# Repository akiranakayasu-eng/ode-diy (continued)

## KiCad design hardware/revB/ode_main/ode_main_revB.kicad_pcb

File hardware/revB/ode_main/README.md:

# ode_main rev B（ESP32-S3 Wi-Fi 一体版）回路図 6 版・PCB 4 版（2026-11-23）

構成案: 構成案_revB_ESP32-S3_v1.md（同じフォルダ）。ケースは case/ と 構成案_revB.md（v0）。

## 状態

- 回路図 6 版: ERC 0（kicad-cli 10.0、docker）、設計意図との照合 0（verify.txt: 365 ピン / 70 ネット）。6 版は 5 版に R87 を足しただけ
- 1 版は別スレッドでチェック済み（回路図チェック_別スレッド_2026-11-19.md、高 0・中 4・低 9）。2 版の変えた所も別スレッドでチェック済み（変更点チェック_2版_別スレッド_2026-11-19.md、高 0・中 1・低 4）。3 版の変えた所も別スレッドでチェック済み（変更点チェック_3版_別スレッド_2026-11-19.md、高 0・中 0・低 3）。4 版はその低 3 件を直した版で、4 版の変えた所も別スレッドでチェック済み（変更点チェック_4版_別スレッド_2026-11-19.md、高 0・中 0・低 1。低 1 は下の残りの確認 4）。5 版は天板へ出る線に保護を足した版で、**5 版で変えた所は別スレッドのチェック待ち**（PCB のチェックと一緒に頼む）
- PDF: ode_main_revB.pdf
- PCB 1 版は別スレッドでチェック済み（PCBチェック_1版_別スレッド_2026-11-23.md、高 0・中 5・低 11。5 版の回路図の変えた所は中以上なし）
- PCB 2 版は別スレッドで変えた所をチェック済み（変更点チェック_PCB2版_別スレッド_2026-11-23.md、高 0・中 0・低 7）
- PCB 3 版（2026-11-23）: 2 版のチェックの低 2・3・6 を直した版。変えた所は別スレッドでチェック済み（高 0・中 0・低 1）
- PCB 4 版（2026-11-23）: 3 版のチェックの低 1 を直した版。下の「PCB 4 版で変えた所」。変えた所と SPI・UART の配線は別スレッドでチェック済み（高 0・中 0・低 3、下の「PCB 4 版のチェックで残した点」）。部品の購入・基板の発注は延期中

## 中身

| 部分 | 部品 | 内容 |
|---|---|---|
| マイコン | U1 ESP32-S3-WROOM-1-N16R8 | 3V3 に 22µF + 0.1µF、EN に 10k/1µF（データシート図 7）。SW1 RESET（EN）、SW3 BOOT（IO0） |
| 有線 LAN | U3 W5500、Y2 25MHz、J5 RJMG1BD3B8K1ANR | WIZnet W5500-Ref-RJ45WithMag に合わせた。SPI は IO10 CS / IO11 MOSI / IO12 SCLK / IO13 MISO、IO14 INT、IO9 RST |
| DMX | U7・U9 74AHCT1G125、U11 ADM2587E、J11 XLR3、J12 XH3 | IO17 = TX（R82 0Ω を通して TX_M、R78 プルアップ）、IO21 = DE（R74 プルダウン）。rev A と同じ周辺 |
| 電源 | J1 USB-C、U5 USBLC6、F1 PICOSMDC110S-2（秋月 113955、1.1A・6V、0805。rev B 構成案 v0 の決定）、Q1 突入制限、U6 MCP1826 | rev A と同じ。FB2 で W5500 の AVDD（+3V3A）を分ける |
| 天板 | J6 JST PH 8P | 1 +3V3 / 2 GND / 3 EN_PANEL / 4 BTN_LOCK / 5 LED_LAN / 6 LED_DMX / 7 LED_LOCK / 8 予備。LOCK は R83 1k＋C78 100n、LED は R84〜R86 100Ω を通して IO4〜IO7 へ。天板の回路図は ../ode_top_revB |
| その他 | D4 PWR、D6 STAT（IO18）、J4 UART0 ログ（R77 499Ω）、CC1/CC2 を R80・R81 22k を通して IO1/IO2 の ADC へ（C74・C75 100n） | |

ピン割り当ての理由と出典は構成案の「ピン割り当て案」。IO35〜37（PSRAM）と IO0・IO3・IO45・IO46（起動ピン）の扱いもそこに書いた。

## 2 版で変えた所（1 版のチェックを受けて）

| 指摘 | 変えた所 |
|---|---|
| 中 1 | U3 23 番（RSVD）を GND へ（W5500 データシート表 2「must be tied to GND」） |
| 中 2 | 受信の終端 R71・R72 を W5500 側（ETH_RXP・ETH_RXN）と RCT の間へ移した（WIZnet 参考回路のとおり） |
| 中 3 | F1 の値を PICOSMDC110S-2 にした（0805 は rev B 構成案 v0 の決定どおり。秋月 113955: 1.1A、トリップ 2.2A、6V） |
| 中 4 | 天板の J6.3 は R79 1kΩ を通して EN へ（ネット EN_PANEL） |
| 低 1 | DE を IO18 → IO21、STAT を IO21 → IO18 に入れ替え |
| 低 2 | TX_M に R78 10k プルアップ |
| 低 3 | USB D+／D− に R4・R5（0Ω）、ネット USB_DP_M・USB_DM_M |
| 低 4 | W5500 SCLK に R76（0Ω）と C69（未実装） |
| 低 5 | UART0 TX に R77 499Ω |
| 低 6 | W5500 XO と水晶の間に R62（0Ω） |
| 低 8 | CC1・CC2 を IO1・IO2（ADC）へ |
| 低 7・低 9 | 低 7（R8 は rev A と同じ GND）は変えない。低 9（LDO の発熱）は PCB で見る |

## 3 版で変えた所（2 版の変更点チェックを受けて）

| 指摘 | 変えた所 |
|---|---|
| 中 1 | CC1・CC2 と IO1・IO2 の間に R80・R81（22k）、ESP32 側に C74・C75（→ GND。3 版は 10nF、4 版で 100nF）。ネット CC1_ADC・CC2_ADC |
| 低 1 | R60 1MΩ を X25_IN–X25_XO（W5500 の XI–XO ピンの間）へ移した（W5500 図 3、WIZnet 参考回路） |
| 低 2 | USB D+／D− に C76・C77（未実装、→ GND）の場所（3 版は ESP32 側、4 版でコネクタ側へ） |
| 低 3 | IO17（ネット TX_U）と TX_M の間に R82（0Ω） |
| 低 4 | J4 の GND を右へ出して、ラベルと重ならないようにした（見た目だけ） |

## 4 版で変えた所（3 版の変更点チェックを受けて）

| 指摘 | 変えた所 |
|---|---|
| 低 1 | C76・C77 を USB_DP・USB_DM（R4・R5 と U5 の間、コネクタ側）へ移した（設計ガイドの USB の図、モジュールの図 7） |
| 低 2 | C74・C75 を 10nF → 100nF（設計ガイド ADC「0.1 μF」） |
| 低 3 | J6 の GND を右へ出して、ラベルと重ならないようにした（見た目だけ） |

## 5 版で変えた所（2026-11-23、作ったスレッドで足した）

| 理由 | 変えた所 |
|---|---|
| 天板は手で触れる板なので、ケーブルの先のピンを ESP32 に直結しない（2 版チェック中 1 と同じ考え） | J6.4 BTN_LOCK と IO7 の間に R83 1k、IO7 側に C78 100n（ESD とチャタリング）。ネット BTN_LOCK_M |
| 同上 | J6.5〜7 の LED 線と IO4〜IO6 の間に R84〜R86 100Ω。ネット LED_*_M。LED の電流は 680＋100Ω で約 1.7mA |

## PCB 4 版のチェックで残した点（低 3、どれも直さずに残した）

1. 裏の MISO が W5500 の水晶の真下を通る。間に内層の GND と +3V3 があるので影響は小さい。
2. SCLK の直列抵抗 R76 が W5500 側にある。ダンピングの抵抗なら ESP32 側が良い。今は 0Ω なので実害はない。必要になったら次の版で寄せる。
3. UART の 2 本がモジュールの下をアンテナと平行に約 16mm 通る。ログ用で低速なので、そのままにした。

## PCB 4 版で変えた所（PCB 3 版チェック 低 1）

| チェックの項目 | 変えた所 |
|---|---|
| 裏の GND ベタの細長い切れ端の上側約 24mm にビアがない | その上側は幅 0.3mm でビアが打てなかった。外層の GND ベタの最小幅を 0.25 → 0.5mm にして、細い帯を塗らないようにした。残った 16mm の部分にはビアが 3 本。切れ端用のビアは長さ 6mm に 1 本以上にした |
| 上の変更で C74・C75 の GND（裏、モジュールの下）に裏のベタが届かなくなった | C74.2 と C75.2 を裏の 0.4mm の線でつなぎ、間に GND ビア (5.04, 81.2) を足した |

- 結果: 未配線 0、DRC エラー 0（警告 5 は同じ種類）、verify_pcb NG 0。配線は作り直したので SPI・UART などの線の道筋は 3 版と少し違う

## PCB 3 版で変えた所（PCB 2 版チェックを受けて）

| チェックの項目 | 変えた所 |
|---|---|
| 低 2 1V2O の線が 21.5mm | 22 番から本体の内側のビア (26.1, 35.9) で裏へ落とし、裏の C53.1 へ手で引いた。5.7mm・ビア 1（gen_pcb.py の V12_ROUTES） |
| 低 3 裏の GND ベタの細長い切れ端 | 塗ったあとに GND のつなぎビアを打つ処理を足した（gen_pcb.py の gnd_stitch）。表裏とも GND のところに 5mm おきに 56 本、ビアが 1 本以下か、長いのに 2 本以下の切れ端に 2 本。裏の切れ端は無くなった |
| 低 6 README の数字 | モジュールの左端を 1.5mm に直した |

- そのままにした所: 低 1 J1 の A4/B9 側の VBUS（0.2mm とビア 4。主な電流は A9/B4 側の太い線を流れ、枝は 0.3A 以下）、低 4 USB の D+／D− のビアの数の差（フルスピード）、低 7 ケースと天板（ケースの奥行きの決定を待って直す）、R77 を U1.37 の近くへ（ログ用で低速）
- 組み立ての順番（低 5）: U1 の下の裏に R32・R80・R81・C74・C75 がある（C78 と C31 もモジュールのすぐ横の裏）。**裏の小物を先に付け、ESP32 モジュールは最後に上からホットガンで付ける**。ホットプレートで下から温めない
- 結果: 未配線 0、DRC エラー 0（警告 5 は同じ種類）、verify_pcb NG 0

## 回路図 6 版で変えた所（PCB 1 版チェック 低 11）

| 理由 | 変えた所 |
|---|---|
| BTN_LOCK が ESP32 の内部プルアップだけだった | R87 10k（+3V3 → BTN_LOCK_M）を足した |

## PCB 2 版で変えた所（PCB 1 版のチェックを受けて）

| チェックの項目 | 変えた所 |
|---|---|
| 中 1 アンテナが基板の角にない | U1 を左後ろの角へ (10.5, 77.25, 180°)。モジュールの外形の左端は基板の左端から 1.5mm（パッドの外端は 1.0mm）、アンテナ部は後ろの辺の外。後ろ左の取り付け穴をやめ、穴は (3.5, 59.5)・(72.5, 58)・(72.5, 80.5)・(49.5, 80.5) |
| 中 2 5V の経路が 0.2mm とビア 1 個 | J1 VBUS → F1 → C1 → Q1 → C3 を F.Cu の手引きで 0.5〜0.8mm（ビアなし）。C3 から U6 の入力までは F.Cu の +5V ゾーン |
| 中 3 LDO の出力がビア 1 個で +3V3 の面へ | U6 の 3 番と C5 を F.Cu の +3V3 ゾーンでつなぎ、In2 へのビアを 5 個 |
| 中 4 LDO の放熱の銅がない | U6 のタブ（GND）の周り約 10 × 10mm を F.Cu の GND ゾーン（直結）にし、In1 へのビアを 21 個 |
| 中 5 TOCAP C54 が遠い | C54 と C53（1V2O）を U3 の 20・22 番の裏へ。距離 1.1mm・2.6mm（1 版は 6.9mm） |
| 低 1 水晶が遠い | Y2 を 30・31 番の真下へ、R60・R62 も寄せた。X25 の配線は 3.5〜8mm でビアなし（1 版は 13〜17mm・ビア 2） |
| 低 4 外層に GND ベタがない | F.Cu と B.Cu の一次側に GND ベタ（優先度は一番下） |
| 低 5 J4・J6 がアンテナの近く | J4 は (22, 60)、J6 は (31.5, 71)。アンテナ部から 10mm 以上 |
| 低 7 シルク | 「ISOLATION 2.5kV」→「ISO」、アンテナの矢印 →「ANTENNA: back edge」、Art-Net の文字をやめて「DMX512 node」 |
| 低 11 | R87 を R83〜R86 の列に置いた（C78 は R83 と R84 の間の裏） |

- 合わせて動かした所: BOOT の SW3 は (35.5, 57)、R32 は 27 番の横の裏、CC の分圧 R80・R81・C74・C75 はモジュールの下の裏、SPI の R76・C69・R66 は U3 の下 (y 49) へ（32〜36 番の引き出しを空けるため）
- 結果: 未配線 0、DRC エラー 0（警告 5 は 1 版と同じ種類）、verify_pcb NG 0
- そのまま残した所: 低 2 Ethernet の対の長さの差（同じ）、低 3 USB 約 80mm（J1 が左前のため。1 版は 108mm）、低 6 C109 の沿面、低 8 AVDD のパスコン 4mm 前後、低 9 LED の色と抵抗（天板の LED を決めてから）、低 10 J6.1 に +3V3 をそのまま出す（天板側で受ける）

## PCB 1 版（2026-11-23、作ったスレッドでの確認まで）

- 76 × 84mm、4 層 FR-4 1.6mm（F.Cu・B.Cu 信号、In1 GND、In2 +3V3）。前の辺に左から USB-C J1、RJ45 J5、XLR3 J11（rev A の左 76mm と同じ位置）。ポート 1 の絶縁の島と帯も rev A と同じ寸法
- U1 ESP32-S3-WROOM-1 は後ろの辺に 180 度で置き、アンテナ部 6mm を基板の外へ出した（ESP32-S3 ハードウェア設計ガイド）
- W5500 U3 は RJ45 の後ろ。1〜12 番（TX/RX）を RJ45 側、水晶と SPI を U1 側に向けた
- U6（LDO）は左の後ろ、F1 は左の前（36mm 離した。docs/電流の見積もり_revB.md）
- 取り付け穴 M3 は (3.5, 45)・(72.5, 58)・(3.5, 80.5)・(72.5, 80.5)（基板の左上が原点、mm）。前の 2 つはコネクタと絶縁の島を避けて後ろへずらした。天板と底板もこれに合わせる
- 自動配線（scripts/route.py、rev A と同じ A*）で未配線 0。DRC はエラー 0、警告 5（U1 と J11 のシルクが基板の端で切れる 4、U1 の EP のビア穴を 0.2→0.3mm にしたためのライブラリとの差 1）
- verify_pcb.txt: パッドのネット照合、ベタのパッドのビア、パスコンの距離、SMD パッドの中のビア 0
- 気になる点（チェックで見てほしい）: Ethernet の対の長さの差（RXP 19.0mm／RXN 12.2mm、RDP 16.5mm／RDN 10.0mm）、USB D+／D− が約 108mm（J1 が左前、U1 の USB ピンが右側のため）、U6 の放熱の銅（まだ広げていない）
- 作り直し: docker kicad/kicad:10.0 の中で `sh scripts/all.sh`（geom → 配線 → 基板 → DRC → 照合）。絵は `bash scripts/render.sh`

## 残っている確認

1. 3.3V の合計電流と U6 の発熱（見積もりは docs/電流の見積もり_revB.md）（ESP32-S3 ピーク 355mA ＋ W5500 約 128mA ＋ LED。5V→3.3V で 1W 近くになりうる）。PCB で放熱の銅を取るか、降圧に替えるか。
2. RJMG1BD3B8K1ANR のトランス仕様（巻数比・インダクタンス）を Amphenol の図面で確かめる（作業環境から読めない）。
3. 天板の基板の回路図は ../ode_top_revB（2026-11-23）。天板の PCB はまだ。
4. F1 の保持電流は 25℃ 1.1A、60℃ 0.8A（秋月 113955 の表、4 版チェックで確認）。5V の合計電流（U6 の 3.3V 側、U11 ADM2587E、U7・U9）を出し、PCB で F1 を LDO から離して置くか、保持電流が上の品にするかを決める。

## 作り直し方

```
export KICAD_SYMDIR=<KiCad 10 の symbols フォルダ>
python3 scripts/gen_sch.py     # 1 回目で .kicad_sym、2 回目で回路図
sh run_erc.sh                  # ERC・ネットリスト・PDF・照合（docker kicad/kicad:10.0）
```

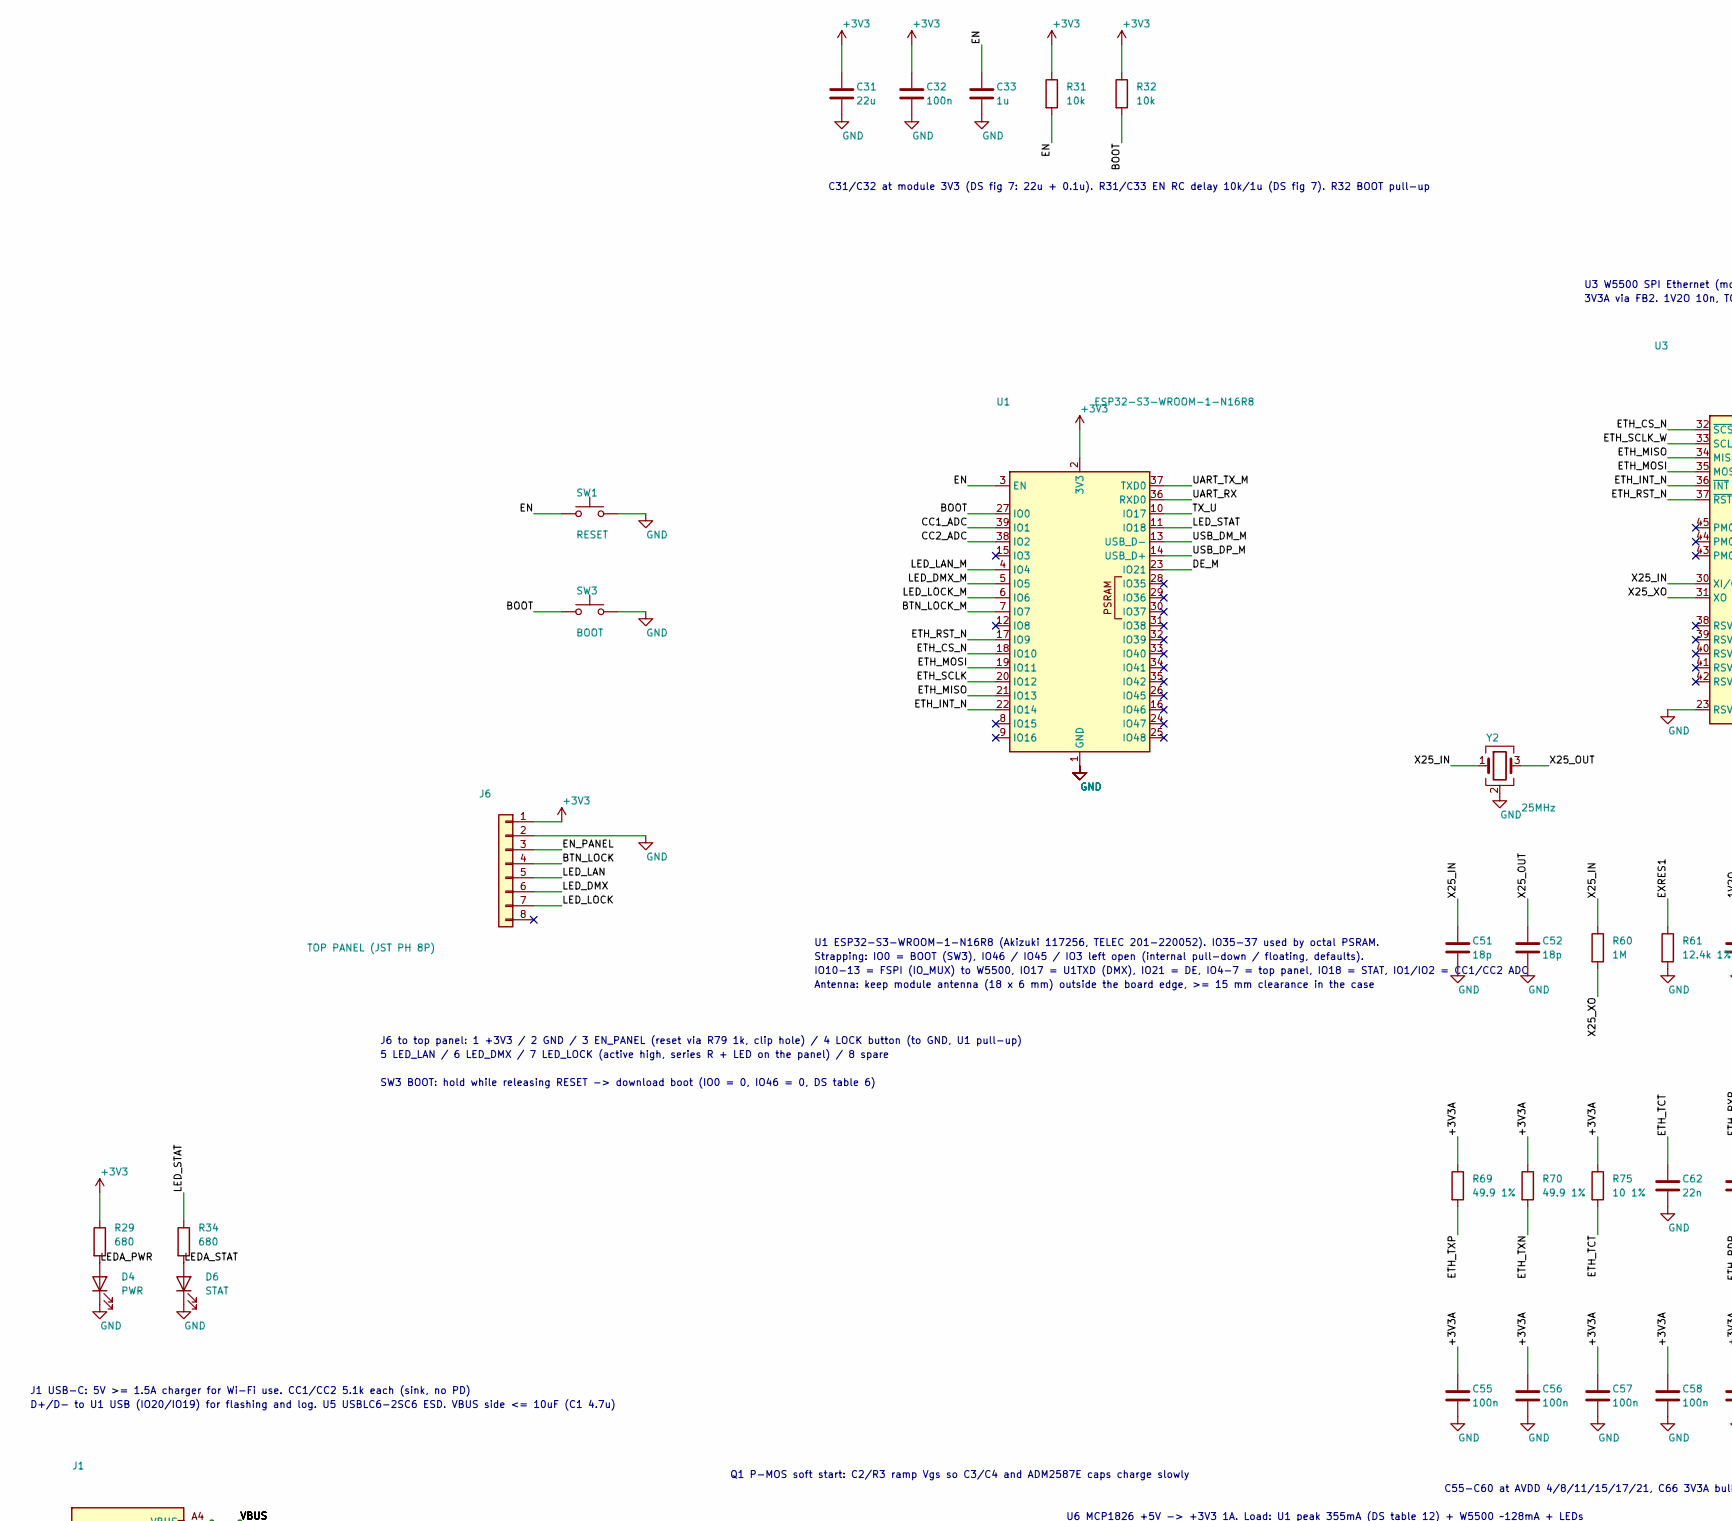
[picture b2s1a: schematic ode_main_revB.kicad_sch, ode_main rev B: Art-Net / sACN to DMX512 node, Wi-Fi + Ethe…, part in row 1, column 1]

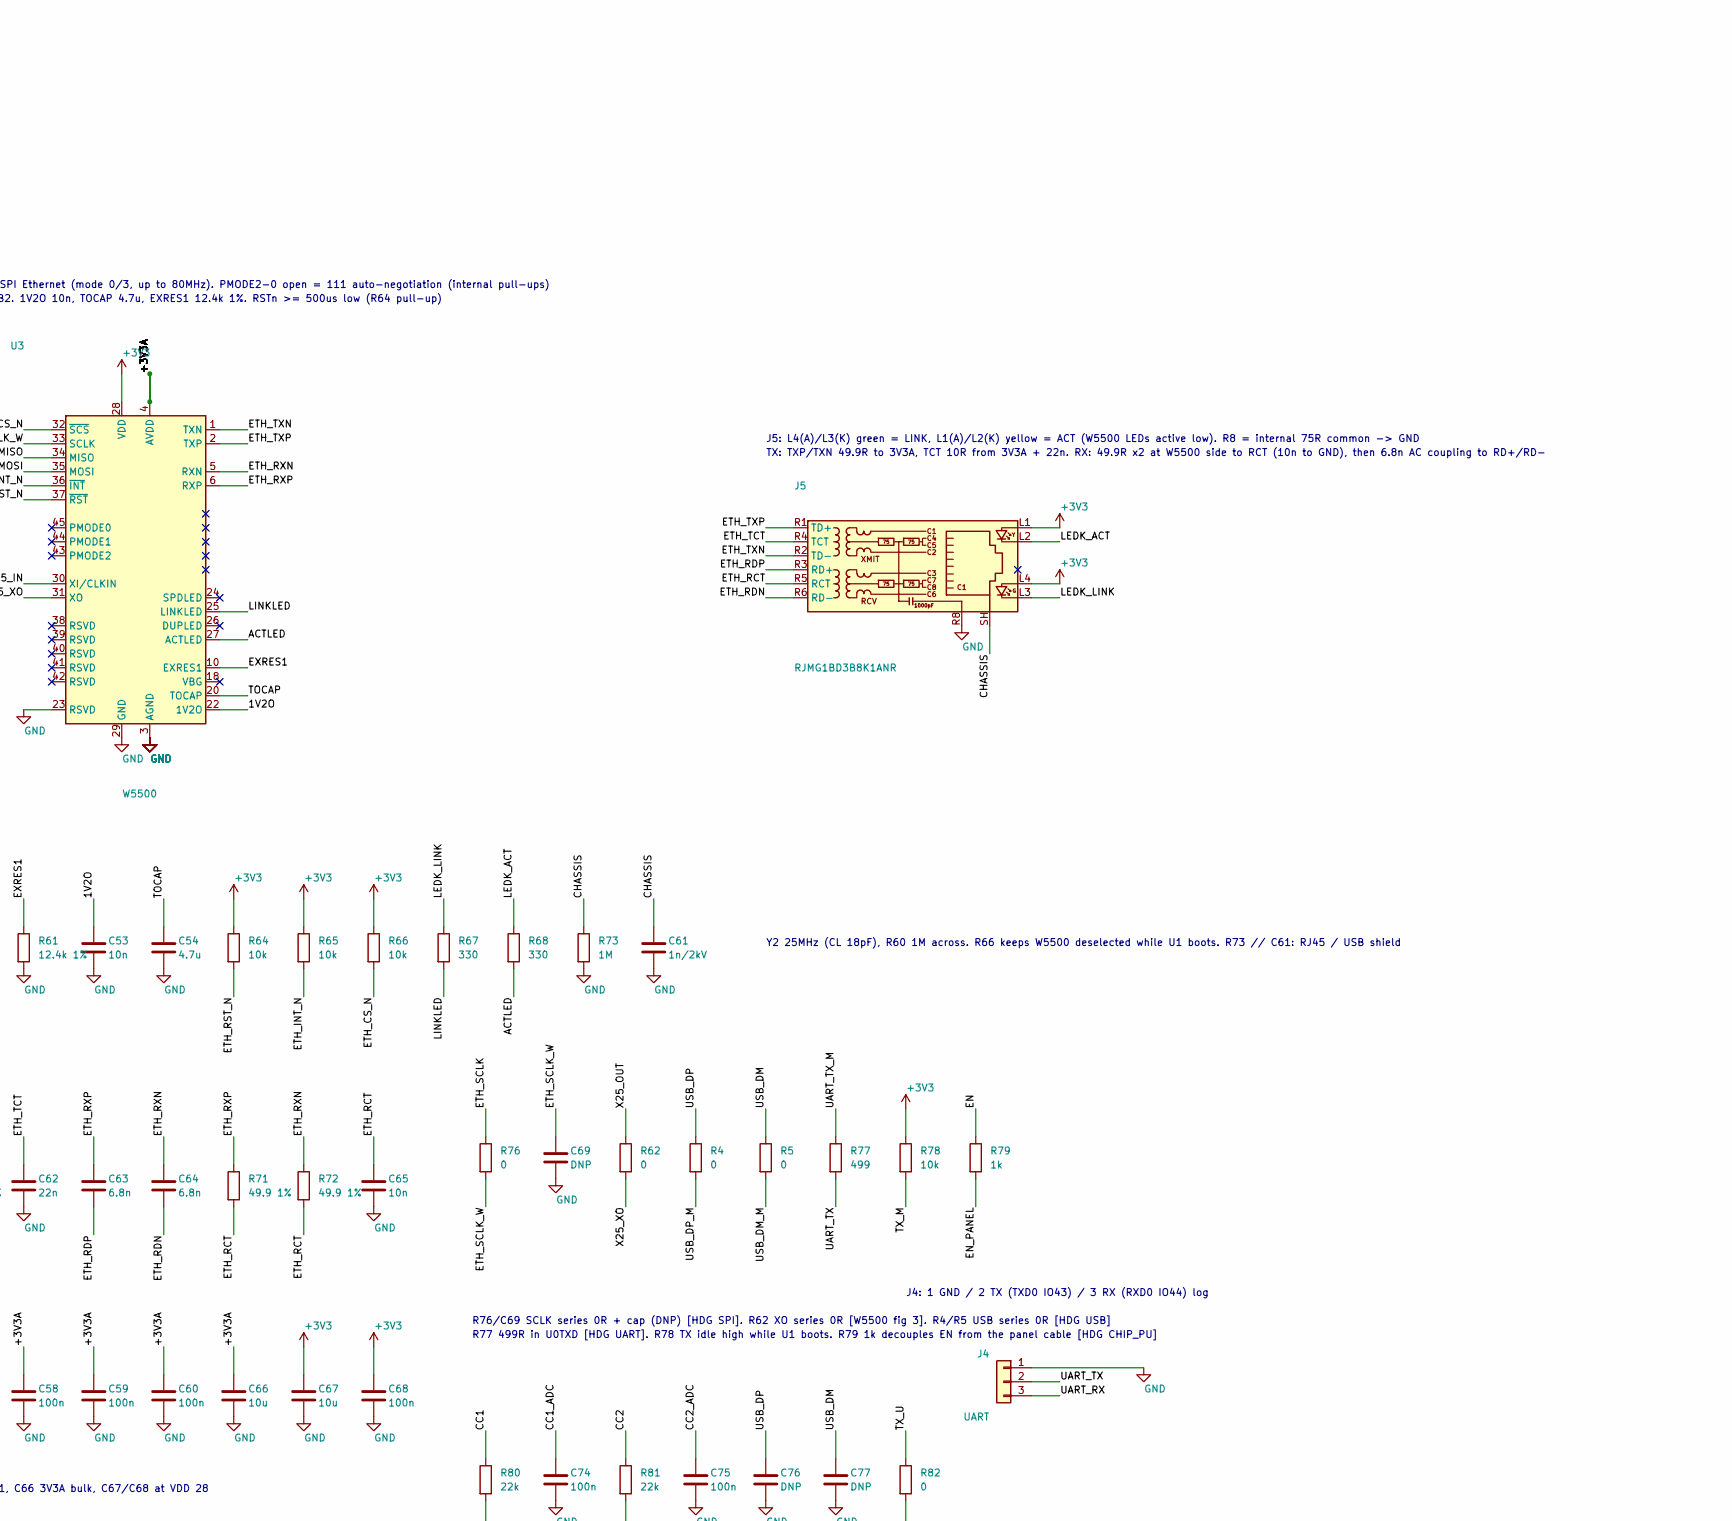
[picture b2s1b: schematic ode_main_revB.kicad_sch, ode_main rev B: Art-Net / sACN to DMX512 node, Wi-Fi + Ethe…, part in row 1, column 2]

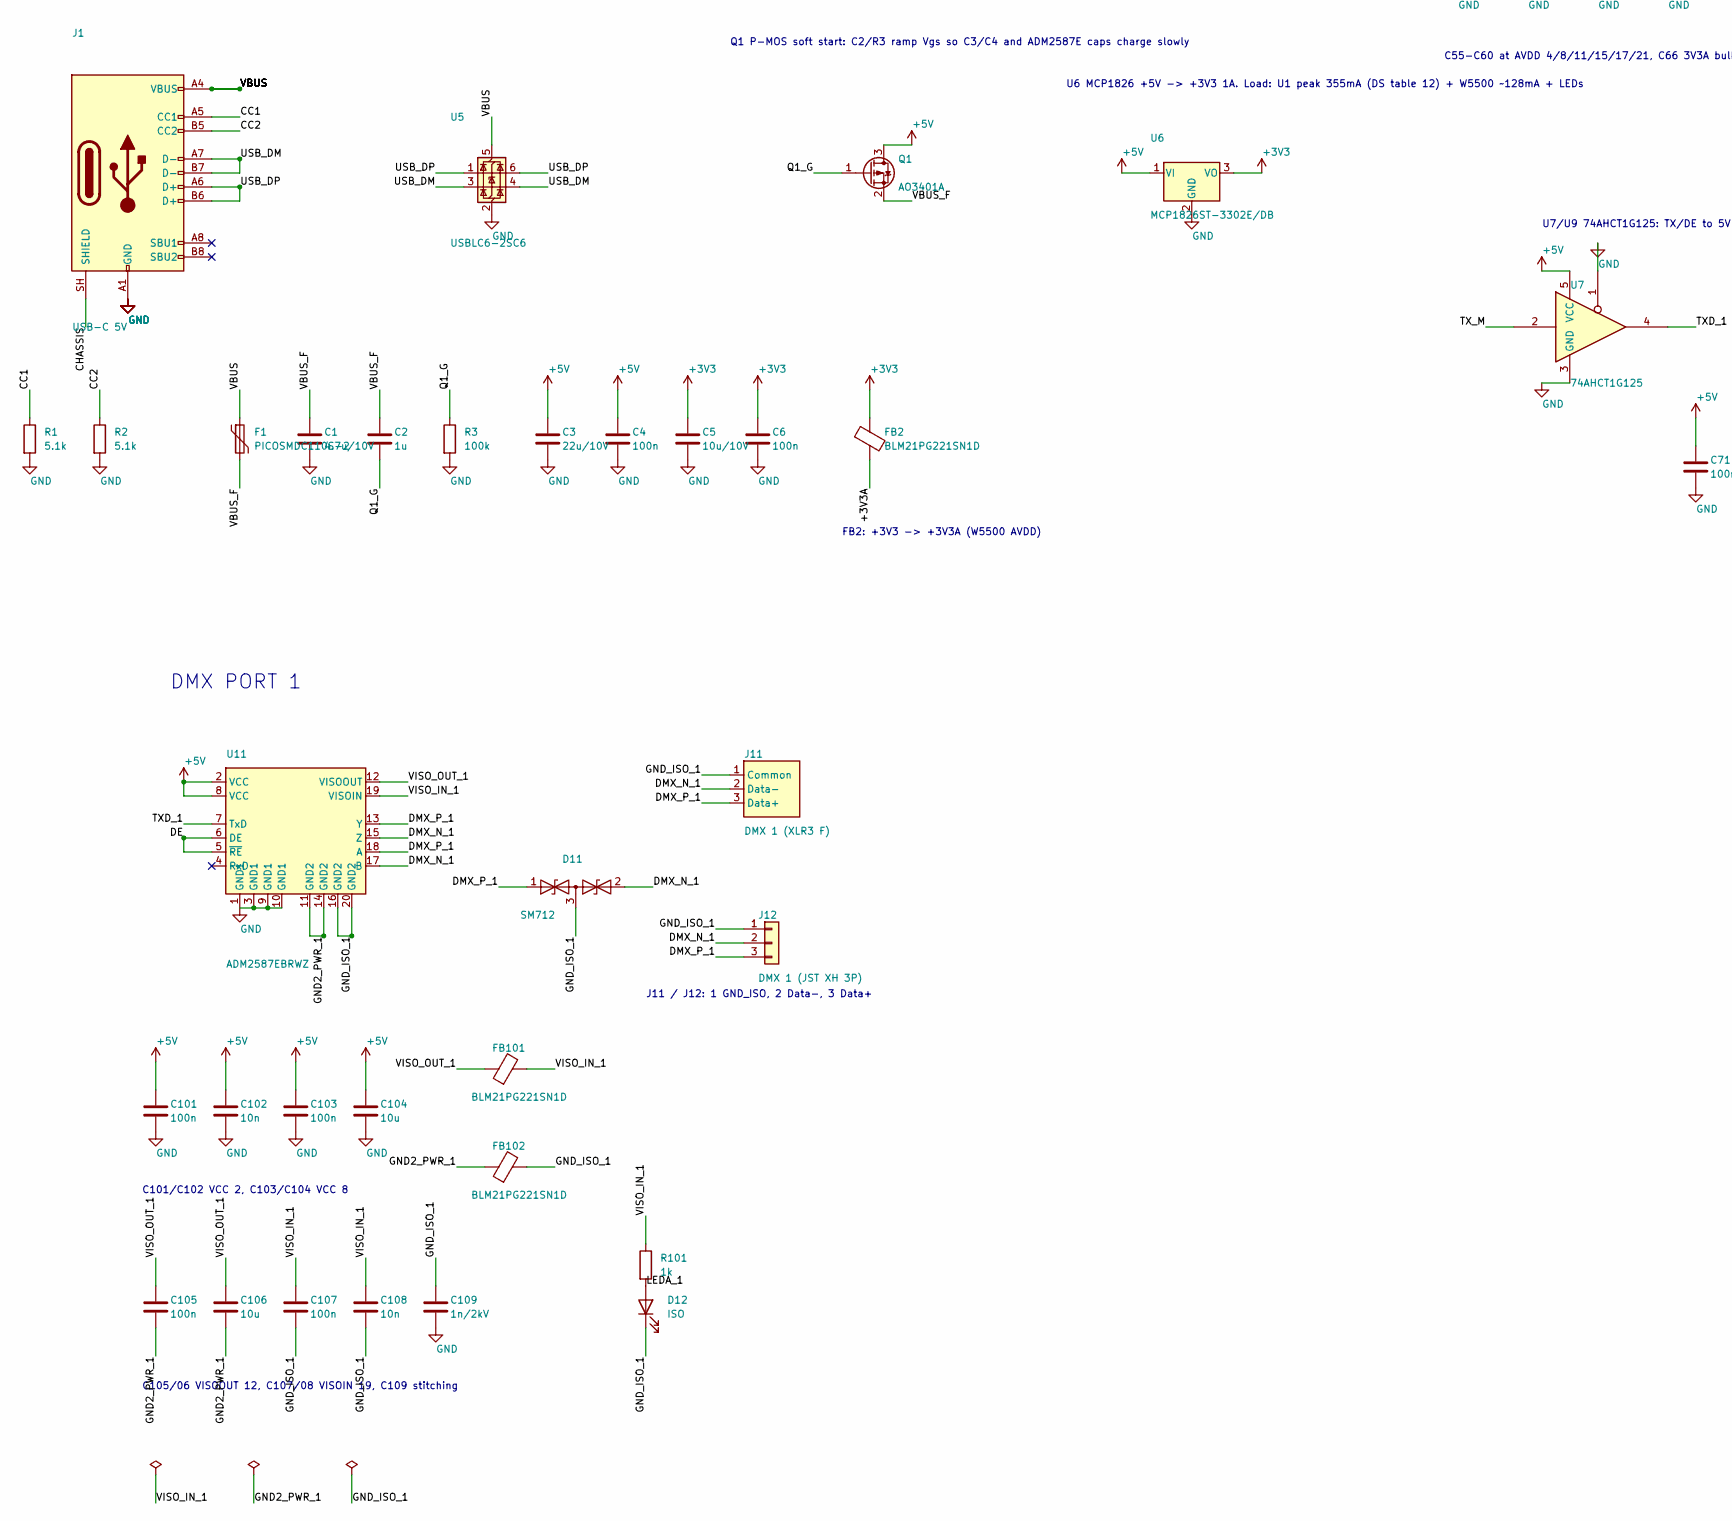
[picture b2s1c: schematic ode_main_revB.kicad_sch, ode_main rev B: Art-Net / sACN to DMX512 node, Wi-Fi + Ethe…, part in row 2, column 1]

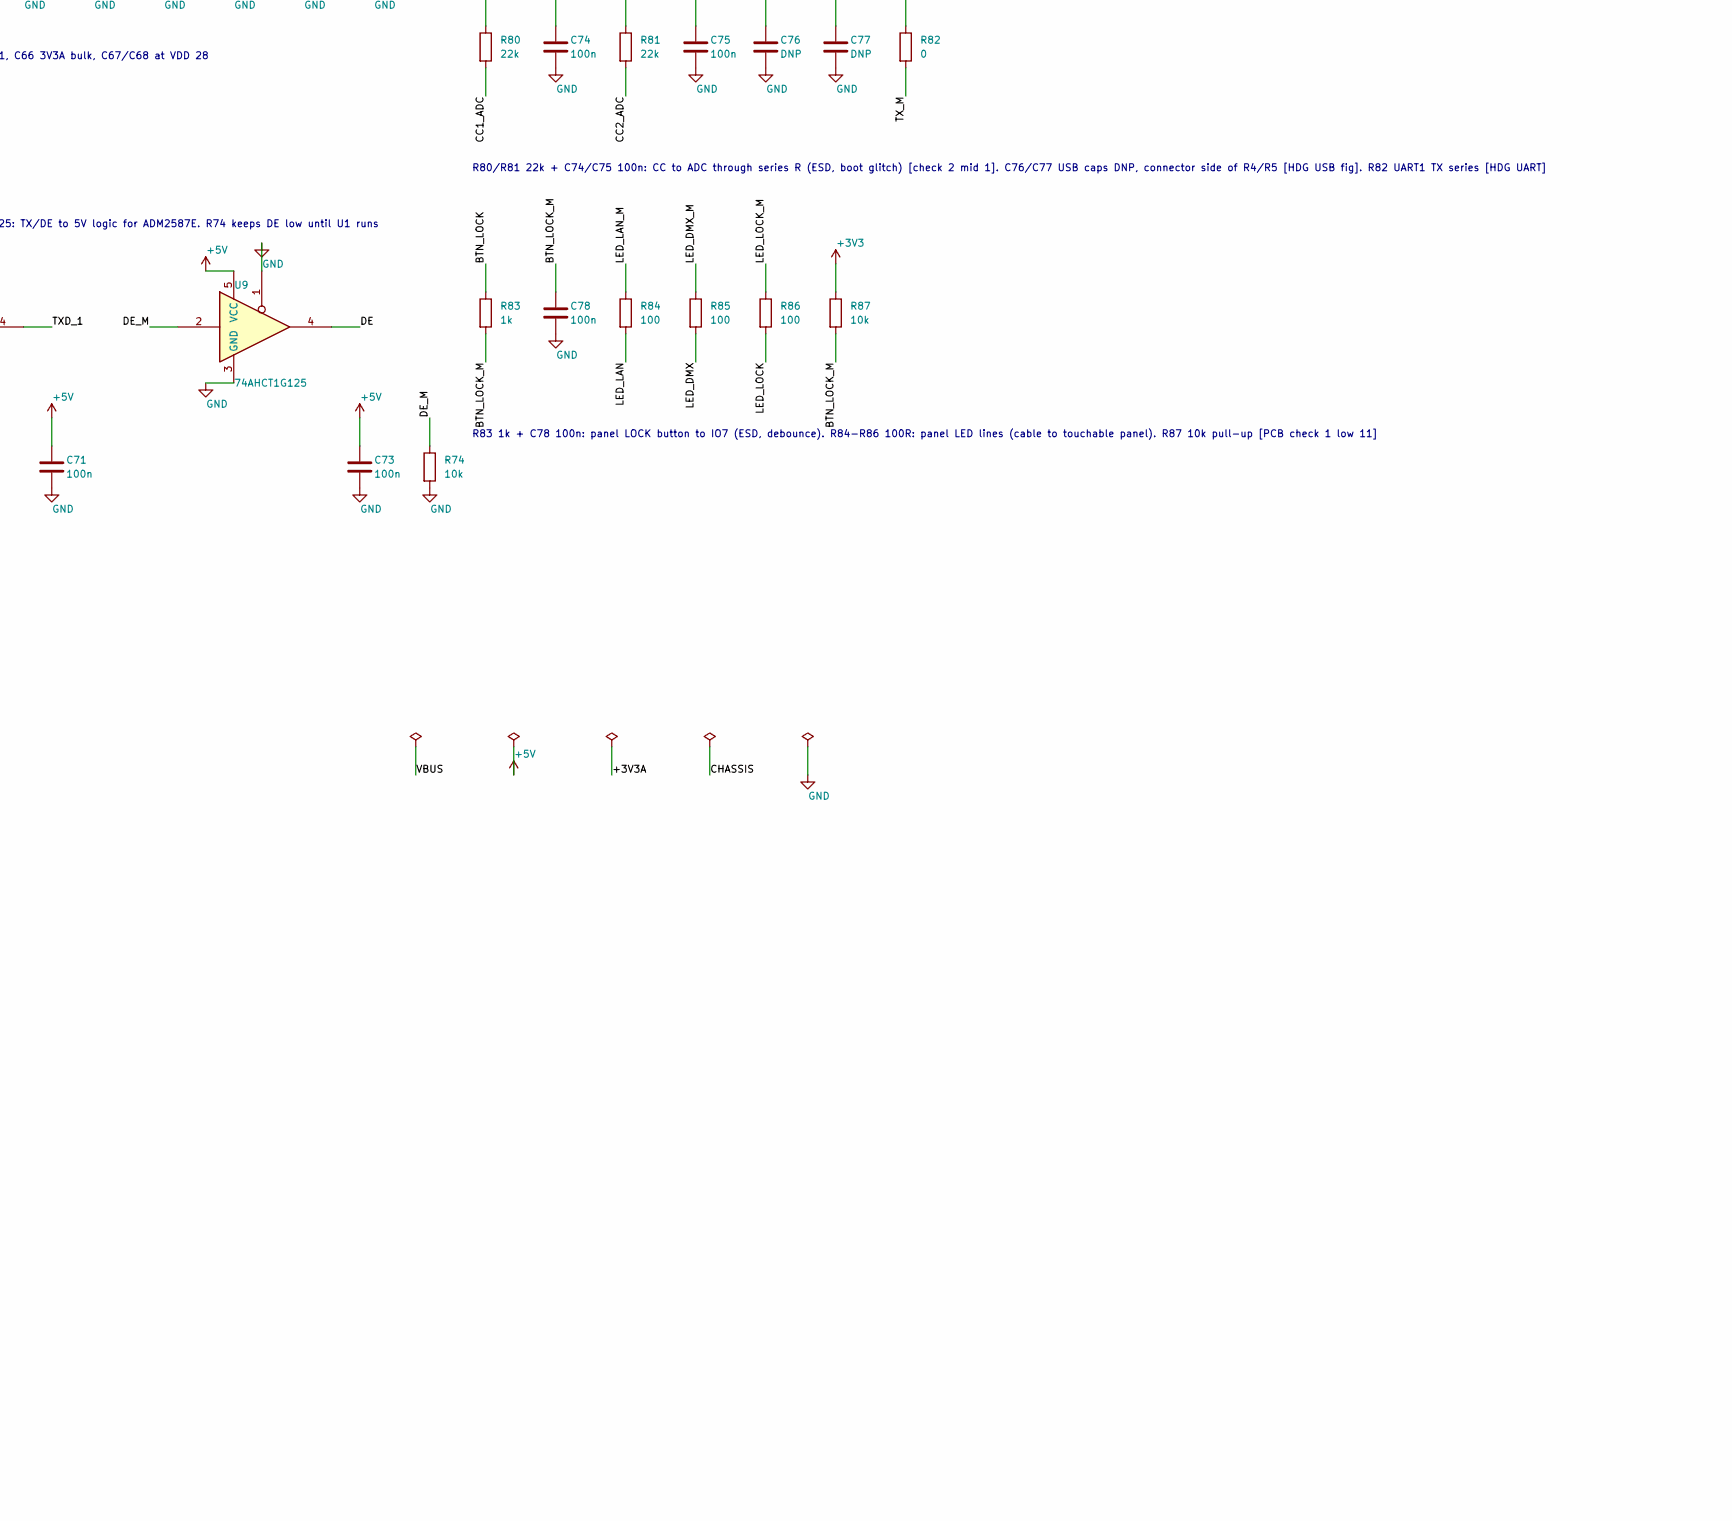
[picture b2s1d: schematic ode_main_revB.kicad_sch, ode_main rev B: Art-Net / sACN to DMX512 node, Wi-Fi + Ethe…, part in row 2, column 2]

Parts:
C1: 4.7u/10V; C_0805_2012Metric_Pad1.18x1.45mm_HandSolder
C2, C33: 1u; C_0805_2012Metric_Pad1.18x1.45mm_HandSolder
C3: 22u/10V; C_1210_3225Metric_Pad1.33x2.70mm_HandSolder
C4, C6, C32, C55, C56, C57, C58, C59, C60, C68, C71, C73, C74, C75, C78, C101, C103, C105, C107: 100n; C_0805_2012Metric_Pad1.18x1.45mm_HandSolder
C5: 10u/10V; C_1210_3225Metric_Pad1.33x2.70mm_HandSolder
C31: 22u; C_1210_3225Metric_Pad1.33x2.70mm_HandSolder
C51, C52: 18p; C_0805_2012Metric_Pad1.18x1.45mm_HandSolder
C53, C65, C102, C108: 10n; C_0805_2012Metric_Pad1.18x1.45mm_HandSolder
C54: 4.7u; C_0805_2012Metric_Pad1.18x1.45mm_HandSolder
C61, C109: 1n/2kV; C_1206_3216Metric_Pad1.33x1.80mm_HandSolder
C62: 22n; C_0805_2012Metric_Pad1.18x1.45mm_HandSolder
C63, C64: 6.8n; C_0805_2012Metric_Pad1.18x1.45mm_HandSolder
C66, C67, C104, C106: 10u; C_0805_2012Metric_Pad1.18x1.45mm_HandSolder
C69, C76, C77: DNP; C_0805_2012Metric_Pad1.18x1.45mm_HandSolder
D4: PWR; LED_0805_2012Metric_Pad1.15x1.40mm_HandSolder
D6: STAT; LED_0805_2012Metric_Pad1.15x1.40mm_HandSolder
D11: SM712; SOT-23
D12: ISO; LED_0805_2012Metric_Pad1.15x1.40mm_HandSolder
F1: PICOSMDC110S-2; Fuse_0805_2012Metric_Pad1.15x1.40mm_HandSolder
FB2, FB101, FB102: BLM21PG221SN1D; L_0805_2012Metric_Pad1.05x1.20mm_HandSolder
J1: USB-C 5V; USB_C_Receptacle_HRO_TYPE-C-31-M-12
J4: UART; PinHeader_1x03_P2.54mm_Vertical
J5: RJMG1BD3B8K1ANR; RJ45_Amphenol_RJMG1BD3B8K1ANR
J6: TOP PANEL (JST PH 8P); JST_PH_B8B-PH-K_1x08_P2.00mm_Vertical
J11: DMX 1 (XLR3 F); Jack_XLR_Neutrik_NC3FAH_Horizontal
J12: DMX 1 (JST XH 3P); JST_XH_B3B-XH-A_1x03_P2.50mm_Vertical
Q1: AO3401A; SOT-23
R1, R2: 5.1k; R_0805_2012Metric_Pad1.20x1.40mm_HandSolder
R3: 100k; R_0805_2012Metric_Pad1.20x1.40mm_HandSolder
R4, R5, R62, R76, R82: 0; R_0805_2012Metric_Pad1.20x1.40mm_HandSolder
R29, R34: 680; R_0805_2012Metric_Pad1.20x1.40mm_HandSolder
R31, R32, R64, R65, R66, R74, R78, R87: 10k; R_0805_2012Metric_Pad1.20x1.40mm_HandSolder
R60, R73: 1M; R_0805_2012Metric_Pad1.20x1.40mm_HandSolder
R61: 12.4k 1%; R_0805_2012Metric_Pad1.20x1.40mm_HandSolder
R67, R68: 330; R_0805_2012Metric_Pad1.20x1.40mm_HandSolder
R69, R70, R71, R72: 49.9 1%; R_0805_2012Metric_Pad1.20x1.40mm_HandSolder
R75: 10 1%; R_0805_2012Metric_Pad1.20x1.40mm_HandSolder
R77: 499; R_0805_2012Metric_Pad1.20x1.40mm_HandSolder
R79, R83, R101: 1k; R_0805_2012Metric_Pad1.20x1.40mm_HandSolder
R80, R81: 22k; R_0805_2012Metric_Pad1.20x1.40mm_HandSolder
R84, R85, R86: 100; R_0805_2012Metric_Pad1.20x1.40mm_HandSolder
SW1: RESET; SW_SPST_TL3342
SW3: BOOT; SW_SPST_TL3342
U1: ESP32-S3-WROOM-1-N16R8; ESP32-S3-WROOM-1
U3: W5500; LQFP-48_7x7mm_P0.5mm
U5: USBLC6-2SC6; SOT-23-6
U6: MCP1826ST-3302E/DB; SOT-223-3_TabPin2
U7, U9: 74AHCT1G125; SOT-23-5
U11: ADM2587EBRWZ; SOIC-20W_7.5x12.8mm_P1.27mm
Y2: 25MHz; Crystal_SMD_3225-4Pin_3.2x2.5mm

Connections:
+3V3: C5.1, C6.1, C31.1, C32.1, C67.1, C68.1, FB2.1, J5.L1, J5.L4, J6.1, R29.1, R31.1, R32.1, R64.1, R65.1, R66.1, R78.1, R87.1, U1.2 (3V3), U3.28 (VDD), U6.3 (VO)
+5V: C3.1, C4.1, C71.1, C73.1, C101.1, C102.1, C103.1, C104.1, Q1.3 (D), U6.1 (VI), U7.5 (VCC), U9.5 (VCC), U11.2 (VCC), U11.8 (VCC)
/1V2O: C53.1, U3.22 (1V2O)
/+3V3A: C55.1, C56.1, C57.1, C58.1, C59.1, C60.1, C66.1, FB2.2, R69.1, R70.1, R75.1, U3.4 (AVDD), U3.8 (AVDD), U3.11 (AVDD), U3.15 (AVDD), U3.17 (AVDD), U3.21 (AVDD)
/ACTLED: R68.2, U3.27 (ACTLED)
/BOOT: R32.2, SW3.1, U1.27 (IO0)
/BTN_LOCK: J6.4, R83.1
/BTN_LOCK_M: C78.1, R83.2, R87.2, U1.7 (IO7)
/CC1: J1.A5 (CC1), R1.1, R80.1
/CC1_ADC: C74.1, R80.2, U1.39 (IO1)
/CC2: J1.B5 (CC2), R2.1, R81.1
/CC2_ADC: C75.1, R81.2, U1.38 (IO2)
/CHASSIS: C61.1, J1.SH (SHIELD), J5.SH, R73.1
/DE: U9.4, U11.5 (~RE), U11.6 (DE)
/DE_M: R74.1, U1.23 (IO21), U9.2
/DMX_N_1: D11.2 (A2), J11.2 (Data-), J12.2, U11.15 (Z), U11.17 (B)
/DMX_P_1: D11.1 (A1), J11.3 (Data+), J12.3, U11.13 (Y), U11.18 (A)
/EN: C33.1, R31.2, R79.1, SW1.1, U1.3 (EN)
/EN_PANEL: J6.3, R79.2
/ETH_CS_N: R66.2, U1.18 (IO10), U3.32 (~SCS)
/ETH_INT_N: R65.2, U1.22 (IO14), U3.36 (~INT)
/ETH_MISO: U1.21 (IO13), U3.34 (MISO)
/ETH_MOSI: U1.19 (IO11), U3.35 (MOSI)
/ETH_RCT: C65.1, J5.R5 (RCT), R71.2, R72.2
/ETH_RDN: C64.2, J5.R6 (RD-)
/ETH_RDP: C63.2, J5.R3 (RD+)
/ETH_RST_N: R64.2, U1.17 (IO9), U3.37 (~RST)
/ETH_RXN: C64.1, R72.1, U3.5 (RXN)
/ETH_RXP: C63.1, R71.1, U3.6 (RXP)
/ETH_SCLK: R76.1, U1.20 (IO12)
/ETH_SCLK_W: C69.1, R76.2, U3.33 (SCLK)
/ETH_TCT: C62.1, J5.R4 (TCT), R75.2
/ETH_TXN: J5.R2 (TD-), R70.2, U3.1 (TXN)
/ETH_TXP: J5.R1 (TD+), R69.2, U3.2 (TXP)
/EXRES1: R61.1, U3.10 (EXRES1)
/GND2_PWR_1: C105.2, C106.2, FB102.1, U11.11 (GND2), U11.14 (GND2)
/GND_ISO_1: C107.2, C108.2, C109.1, D11.3 (common), D12.1 (K), FB102.2, J11.1 (Common), J12.1, U11.16 (GND2), U11.20 (GND2)
/LEDA_1: D12.2 (A), R101.2
/LEDA_PWR: D4.2 (A), R29.2
/LEDA_STAT: D6.2 (A), R34.2
/LEDK_ACT: J5.L2, R68.1
/LEDK_LINK: J5.L3, R67.1
/LED_DMX: J6.6, R85.2
/LED_DMX_M: R85.1, U1.5 (IO5)
/LED_LAN: J6.5, R84.2
/LED_LAN_M: R84.1, U1.4 (IO4)
/LED_LOCK: J6.7, R86.2
/LED_LOCK_M: R86.1, U1.6 (IO6)
/LED_STAT: R34.1, U1.11 (IO18)
/LINKLED: R67.2, U3.25 (LINKLED)
/Q1_G: C2.2, Q1.1 (G), R3.1
/TOCAP: C54.1, U3.20 (TOCAP)
/TXD_1: U7.4, U11.7 (TxD)
/TX_M: R78.2, R82.2, U7.2
/TX_U: R82.1, U1.10 (IO17)
/UART_RX: J4.3, U1.36 (RXD0)
/UART_TX: J4.2, R77.2
/UART_TX_M: R77.1, U1.37 (TXD0)
/USB_DM: C77.1, J1.A7 (D-), J1.B7 (D-), R5.1, U5.3 (I/O2), U5.4 (I/O2)
/USB_DM_M: R5.2, U1.13 (USB_D-)
/USB_DP: C76.1, J1.A6 (D+), J1.B6 (D+), R4.1, U5.1 (I/O1), U5.6 (I/O1)
/USB_DP_M: R4.2, U1.14 (USB_D+)
/VBUS: F1.1, J1.A4 (VBUS), J1.A9 (VBUS), J1.B4 (VBUS), J1.B9 (VBUS), U5.5 (VBUS)
/VBUS_F: C1.1, C2.1, F1.2, Q1.2 (S)
/VISO_IN_1: C107.1, C108.1, FB101.2, R101.1, U11.19 (VISOIN)
/VISO_OUT_1: C105.1, C106.1, FB101.1, U11.12 (VISOOUT)
/X25_IN: C51.1, R60.1, U3.30 (XI/CLKIN), Y2.1
/X25_OUT: C52.1, R62.1, Y2.3
/X25_XO: R60.2, R62.2, U3.31 (XO)
GND: C1.2, C3.2, C4.2, C5.2, C6.2, C31.2, C32.2, C33.2, C51.2, C52.2, C53.2, C54.2, C55.2, C56.2, C57.2, C58.2, C59.2, C60.2, C61.2, C62.2, C65.2, C66.2, C67.2, C68.2, C69.2, C71.2, C73.2, C74.2, C75.2, C76.2, C77.2, C78.2, C101.2, C102.2, C103.2, C104.2, C109.2, D4.1 (K), D6.1 (K), J1.A1 (GND), J1.A12 (GND), J1.B1 (GND), J1.B12 (GND), J4.1, J5.R8, J6.2, R1.2, R2.2, R3.2, R61.2, R73.2, R74.2, SW1.2, SW3.2, U1.1 (GND), U1.40 (GND), U1.41 (GND), U3.3 (AGND), U3.9 (AGND), U3.14 (AGND), U3.16 (AGND), U3.19 (AGND), U3.23 (RSVD), U3.29 (GND), U3.48 (AGND), U5.2 (GND), U6.2 (GND), U7.1, U7.3 (GND), U9.1, U9.3 (GND), U11.1 (GND1), U11.3 (GND1), U11.9 (GND1), U11.10 (GND1), Y2.2 (G), Y2.4 (G)

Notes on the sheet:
U1 ESP32-S3-WROOM-1-N16R8 (Akizuki 117256, TELEC 201-220052). IO35-37 used by octal PSRAM.
Strapping: IO0 = BOOT (SW3), IO46 / IO45 / IO3 left open (internal pull-down / floating, defaults).
IO10-13 = FSPI (IO_MUX) to W5500, IO17 = U1TXD (DMX), IO21 = DE, IO4-7 = top panel, IO18 = STAT, IO1/IO2 = CC1/CC2 ADC
Antenna: keep module antenna (18 x 6 mm) outside the board edge, >= 15 mm clearance in the case
C31/C32 at module 3V3 (DS fig 7: 22u + 0.1u). R31/C33 EN RC delay 10k/1u (DS fig 7). R32 BOOT pull-up
SW3 BOOT: hold while releasing RESET -> download boot (IO0 = 0, IO46 = 0, DS table 6)
J6 to top panel: 1 +3V3 / 2 GND / 3 EN_PANEL (reset via R79 1k, clip hole) / 4 LOCK button (to GND, U1 pull-up)
5 LED_LAN / 6 LED_DMX / 7 LED_LOCK (active high, series R + LED on the panel) / 8 spare
U3 W5500 SPI Ethernet (mode 0/3, up to 80MHz). PMODE2-0 open = 111 auto-negotiation (internal pull-ups)
3V3A via FB2. 1V2O 10n, TOCAP 4.7u, EXRES1 12.4k 1%. RSTn >= 500us low (R64 pull-up)
J5: L4(A)/L3(K) green = LINK, L1(A)/L2(K) yellow = ACT (W5500 LEDs active low). R8 = internal 75R common -> GND
TX: TXP/TXN 49.9R to 3V3A, TCT 10R from 3V3A + 22n. RX: 49.9R x2 at W5500 side to RCT (10n to GND), then 6.8n AC coupling to RD+/RD-
Y2 25MHz (CL 18pF), R60 1M across. R66 keeps W5500 deselected while U1 boots. R73 // C61: RJ45 / USB shield
C55-C60 at AVDD 4/8/11/15/17/21, C66 3V3A bulk, C67/C68 at VDD 28
R83 1k + C78 100n: panel LOCK button to IO7 (ESD, debounce). R84-R86 100R: panel LED lines (cable to touchable panel). R87 10k pull-up [PCB check 1 low 11]
R80/R81 22k + C74/C75 100n: CC to ADC through series R (ESD, boot glitch) [check 2 mid 1]. C76/C77 USB caps DNP, connector side of R4/R5 [HDG USB fig]. R82 UART1 TX series [HDG UART]
R76/C69 SCLK series 0R + cap (DNP) [HDG SPI]. R62 XO series 0R [W5500 fig 3]. R4/R5 USB series 0R [HDG USB]
R77 499R in U0TXD [HDG UART]. R78 TX idle high while U1 boots. R79 1k decouples EN from the panel cable [HDG CHIP_PU]
J4: 1 GND / 2 TX (TXD0 IO43) / 3 RX (RXD0 IO44) log
J1 USB-C: 5V >= 1.5A charger for Wi-Fi use. CC1/CC2 5.1k each (sink, no PD)
D+/D- to U1 USB (IO20/IO19) for flashing and log. U5 USBLC6-2SC6 ESD. VBUS side <= 10uF (C1 4.7u)
Q1 P-MOS soft start: C2/R3 ramp Vgs so C3/C4 and ADM2587E caps charge slowly
U6 MCP1826 +5V -> +3V3 1A. Load: U1 peak 355mA (DS table 12) + W5500 ~128mA + LEDs
FB2: +3V3 -> +3V3A (W5500 AVDD)
U7/U9 74AHCT1G125: TX/DE to 5V logic for ADM2587E. R74 keeps DE low until U1 runs
DMX PORT 1
C101/C102 VCC 2, C103/C104 VCC 8
C105/06 VISOOUT 12, C107/08 VISOIN 19, C109 stitching
J11 / J12: 1 GND_ISO, 2 Data-, 3 Data+

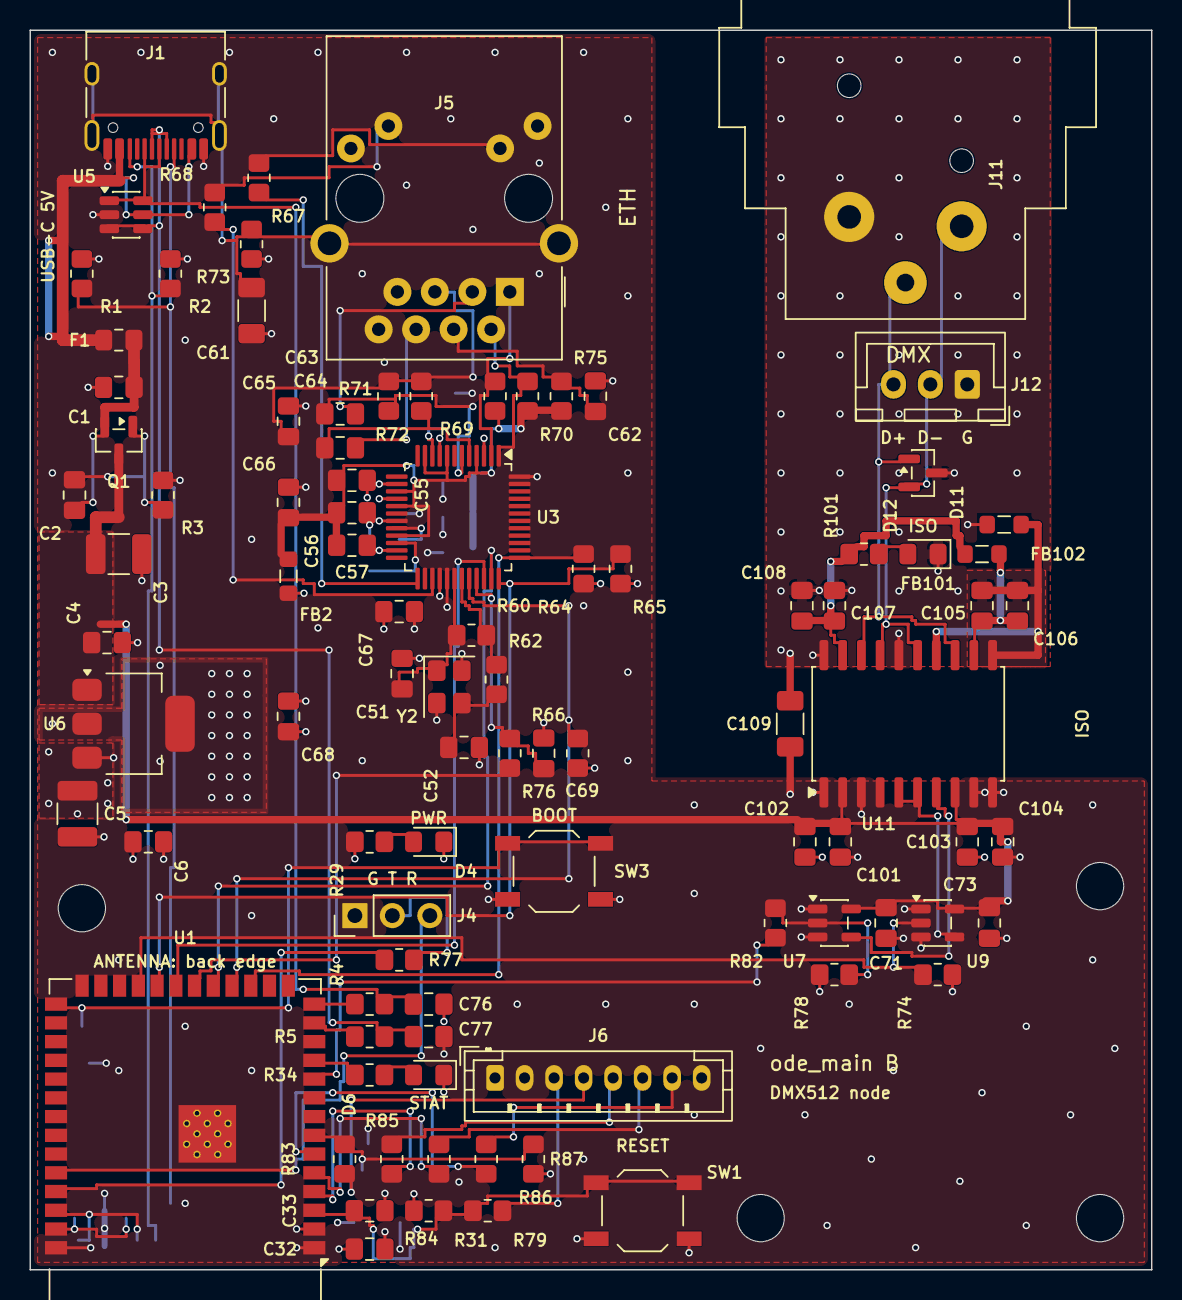
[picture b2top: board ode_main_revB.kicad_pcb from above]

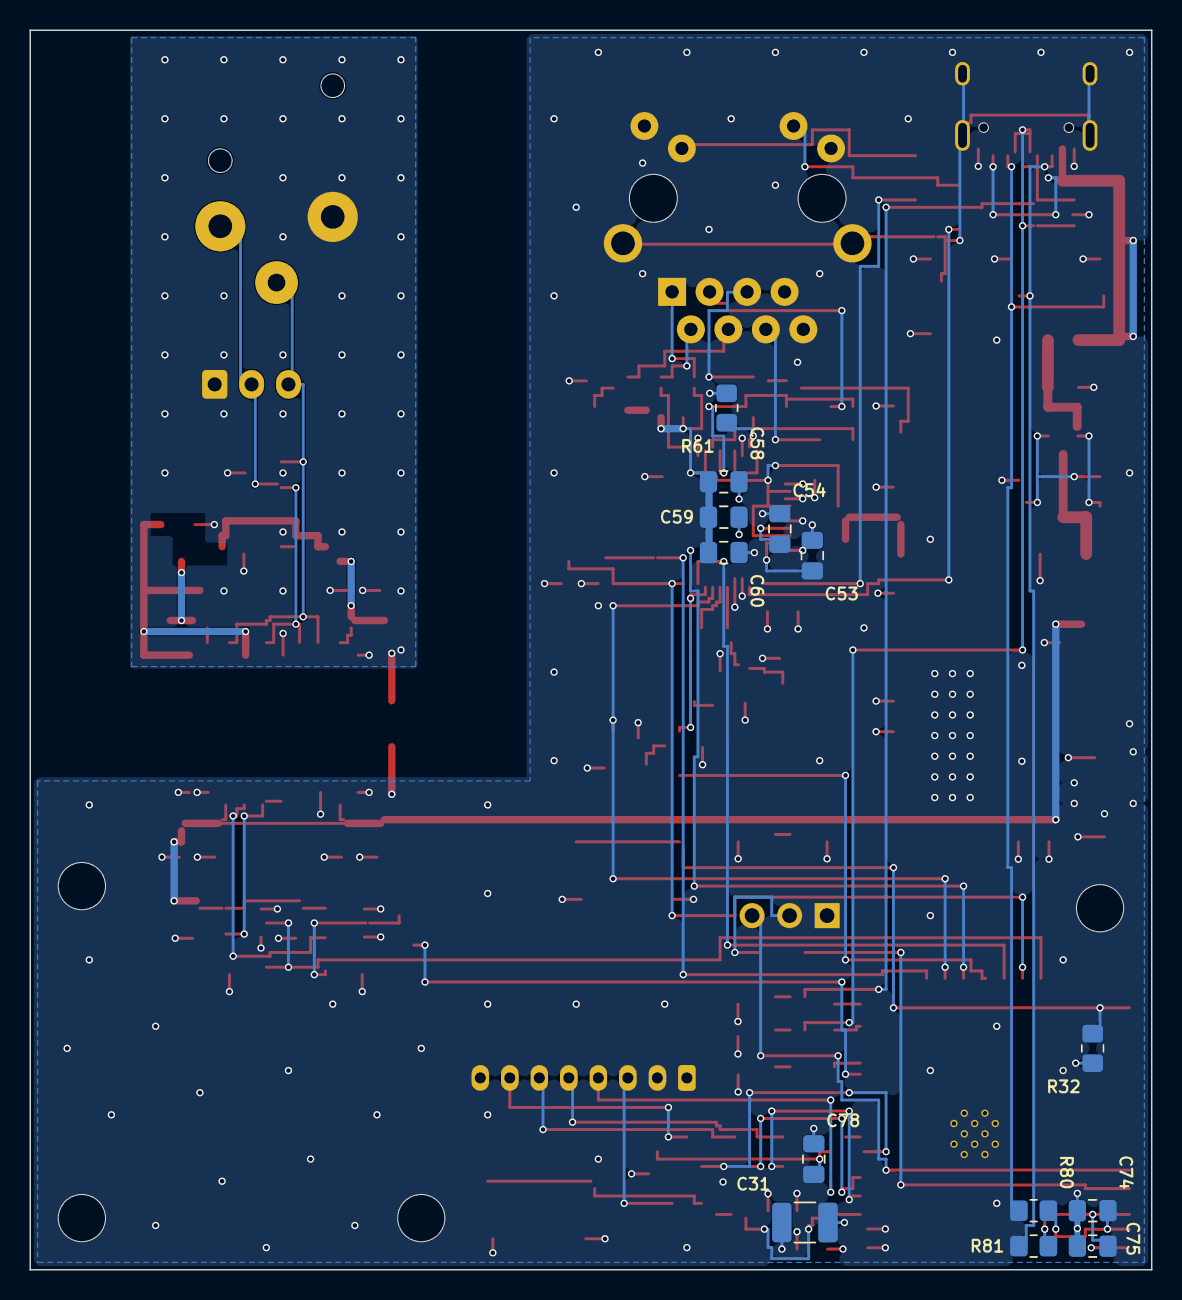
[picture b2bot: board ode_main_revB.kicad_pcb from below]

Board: 4 copper layers, 76.0 x 84.0 mm, 110 parts (13 on the bottom side), 70 nets.

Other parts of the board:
H1, H2, H3, H4: MountingHole_3.2mm_M3
